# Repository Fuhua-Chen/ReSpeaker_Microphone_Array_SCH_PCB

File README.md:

# ReSpeaker_ReSpeaker_Microphone_Array_SCH_PCB
SCH, PCB and assembly files of ReSpeaker Microphone Array

## Requirements  
* Eagle v6.4 or later version

## Structure
* Folder SCH&PCB: sch, PCB and pdf built by Eagle
* Folder Assembly: Gerber, SMT coordinate, Assembly drawings

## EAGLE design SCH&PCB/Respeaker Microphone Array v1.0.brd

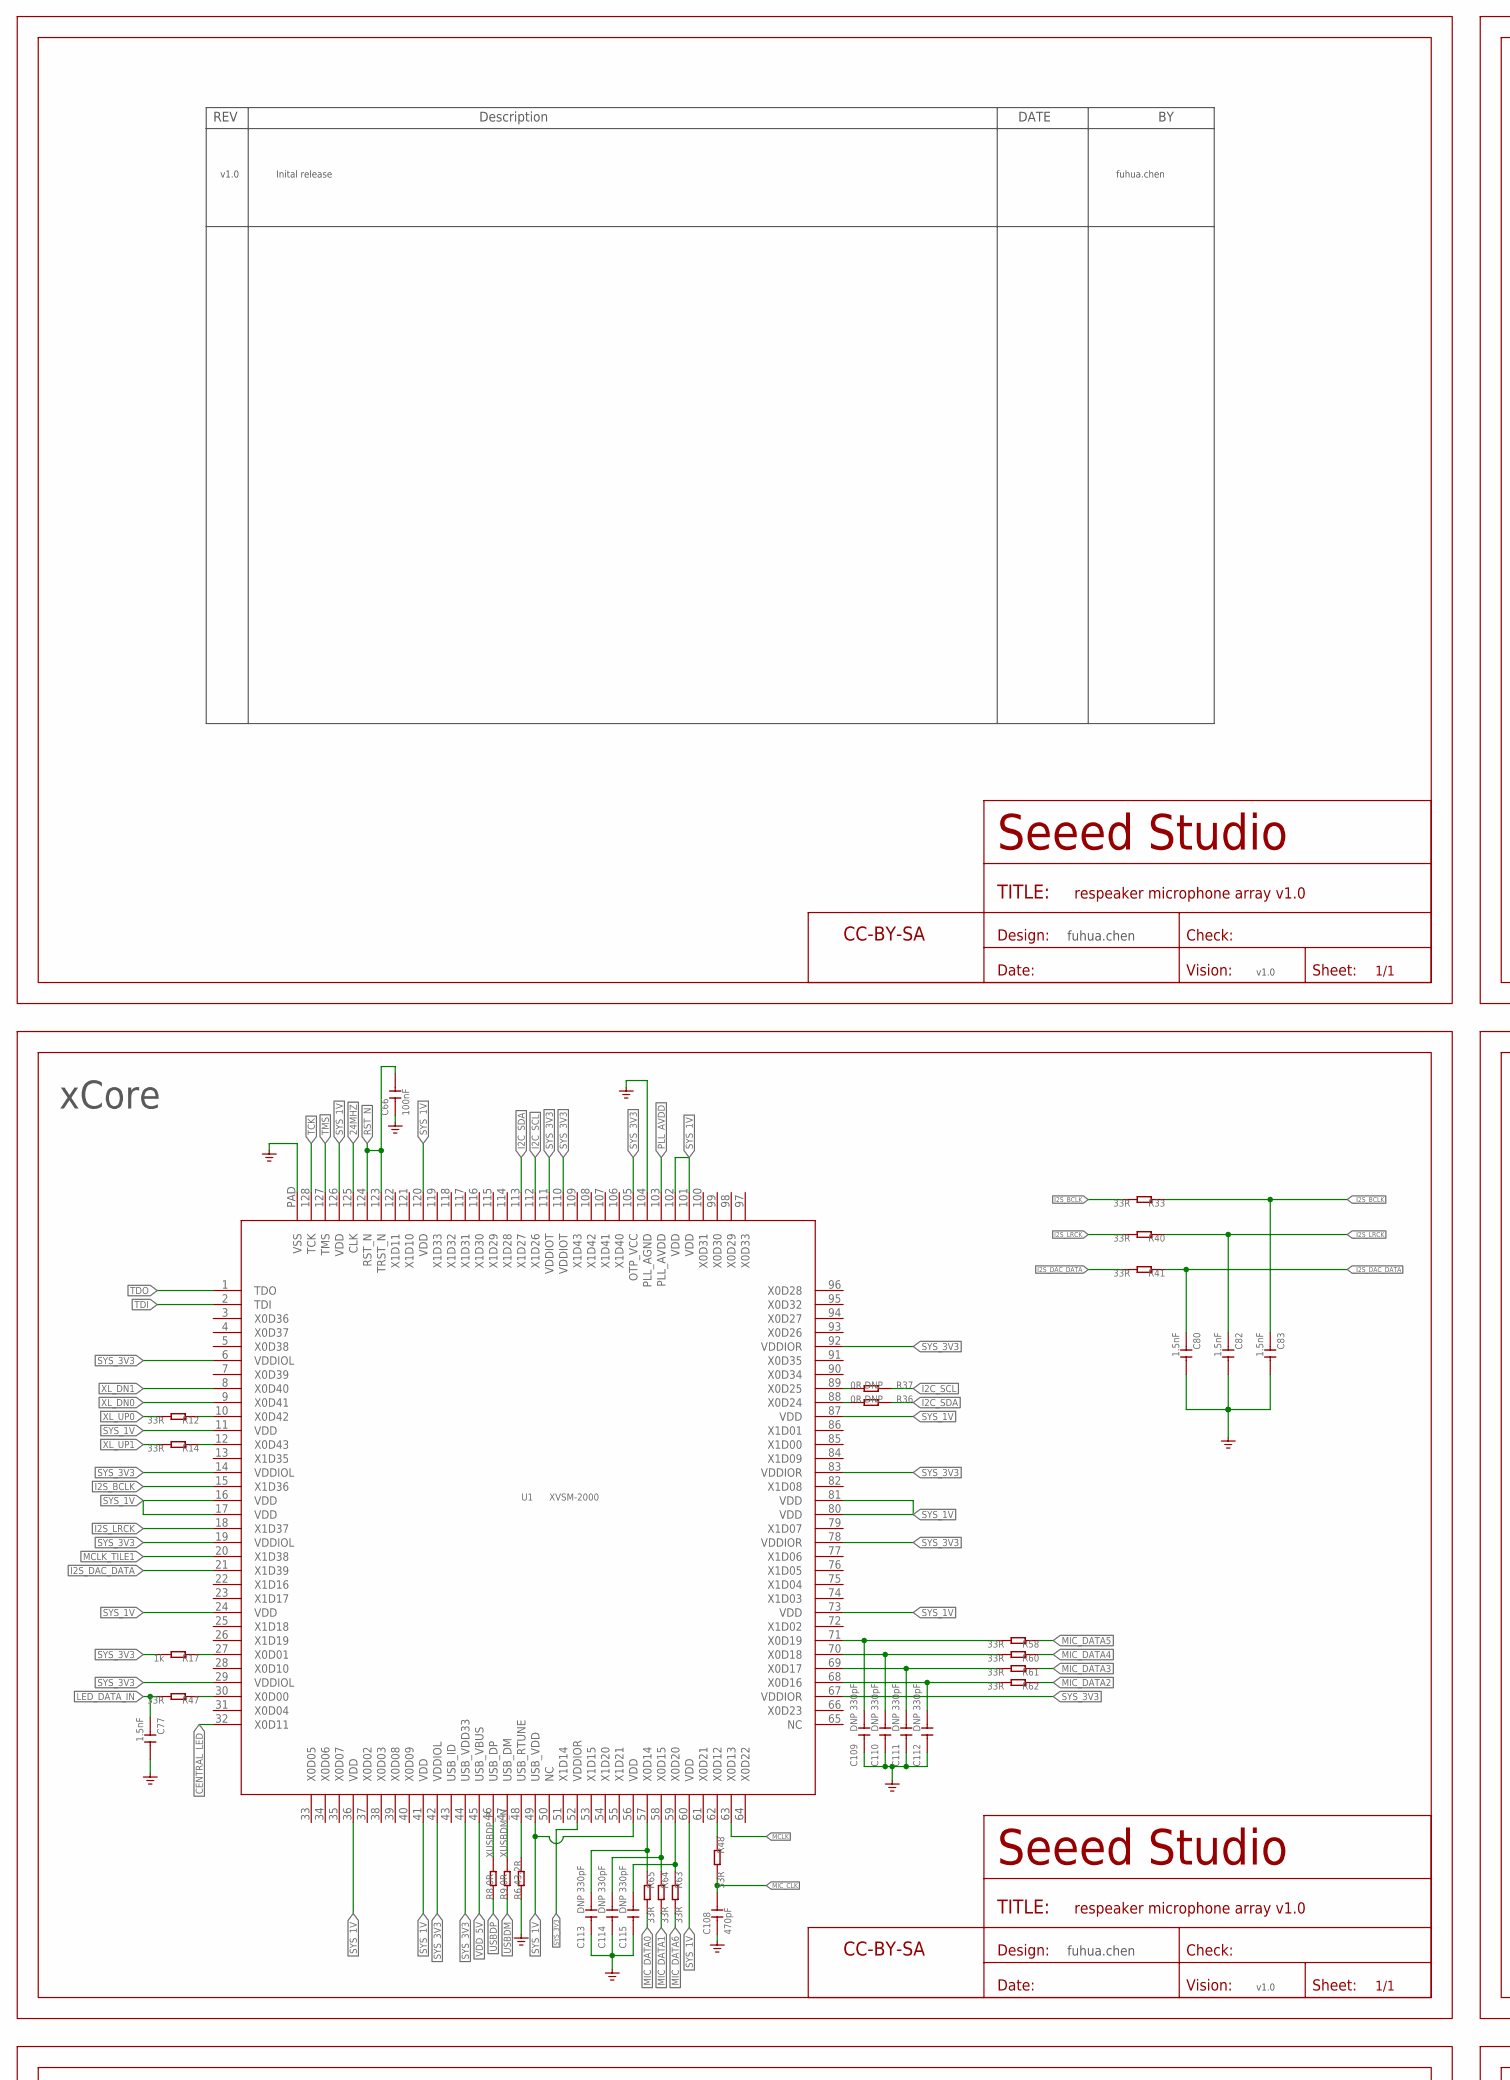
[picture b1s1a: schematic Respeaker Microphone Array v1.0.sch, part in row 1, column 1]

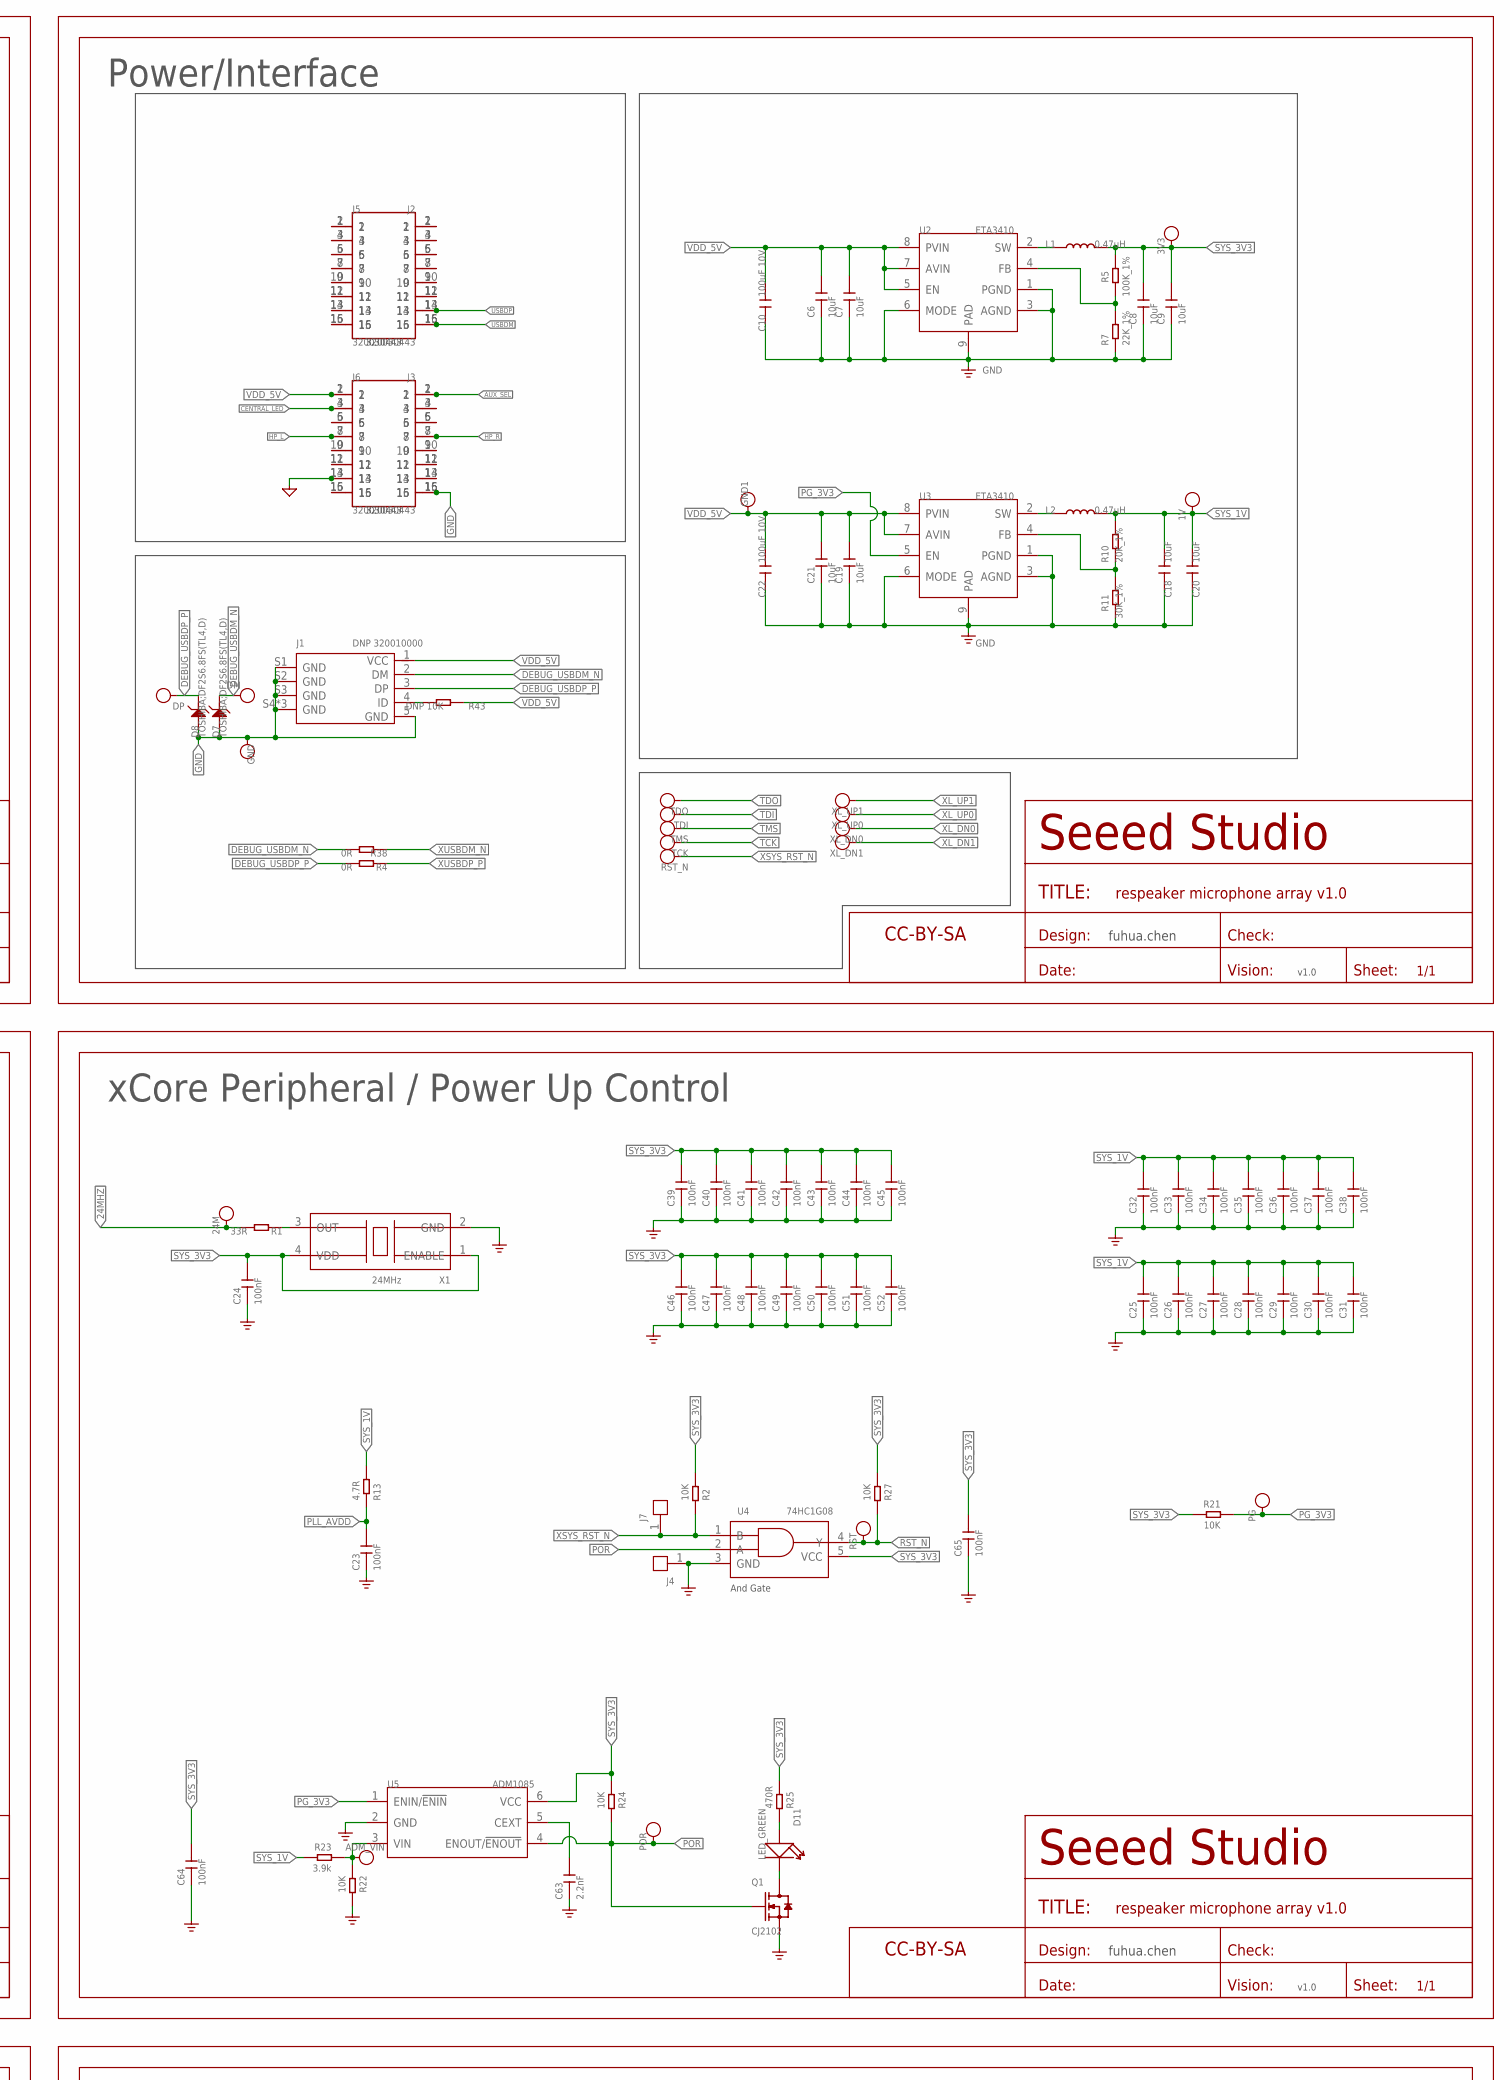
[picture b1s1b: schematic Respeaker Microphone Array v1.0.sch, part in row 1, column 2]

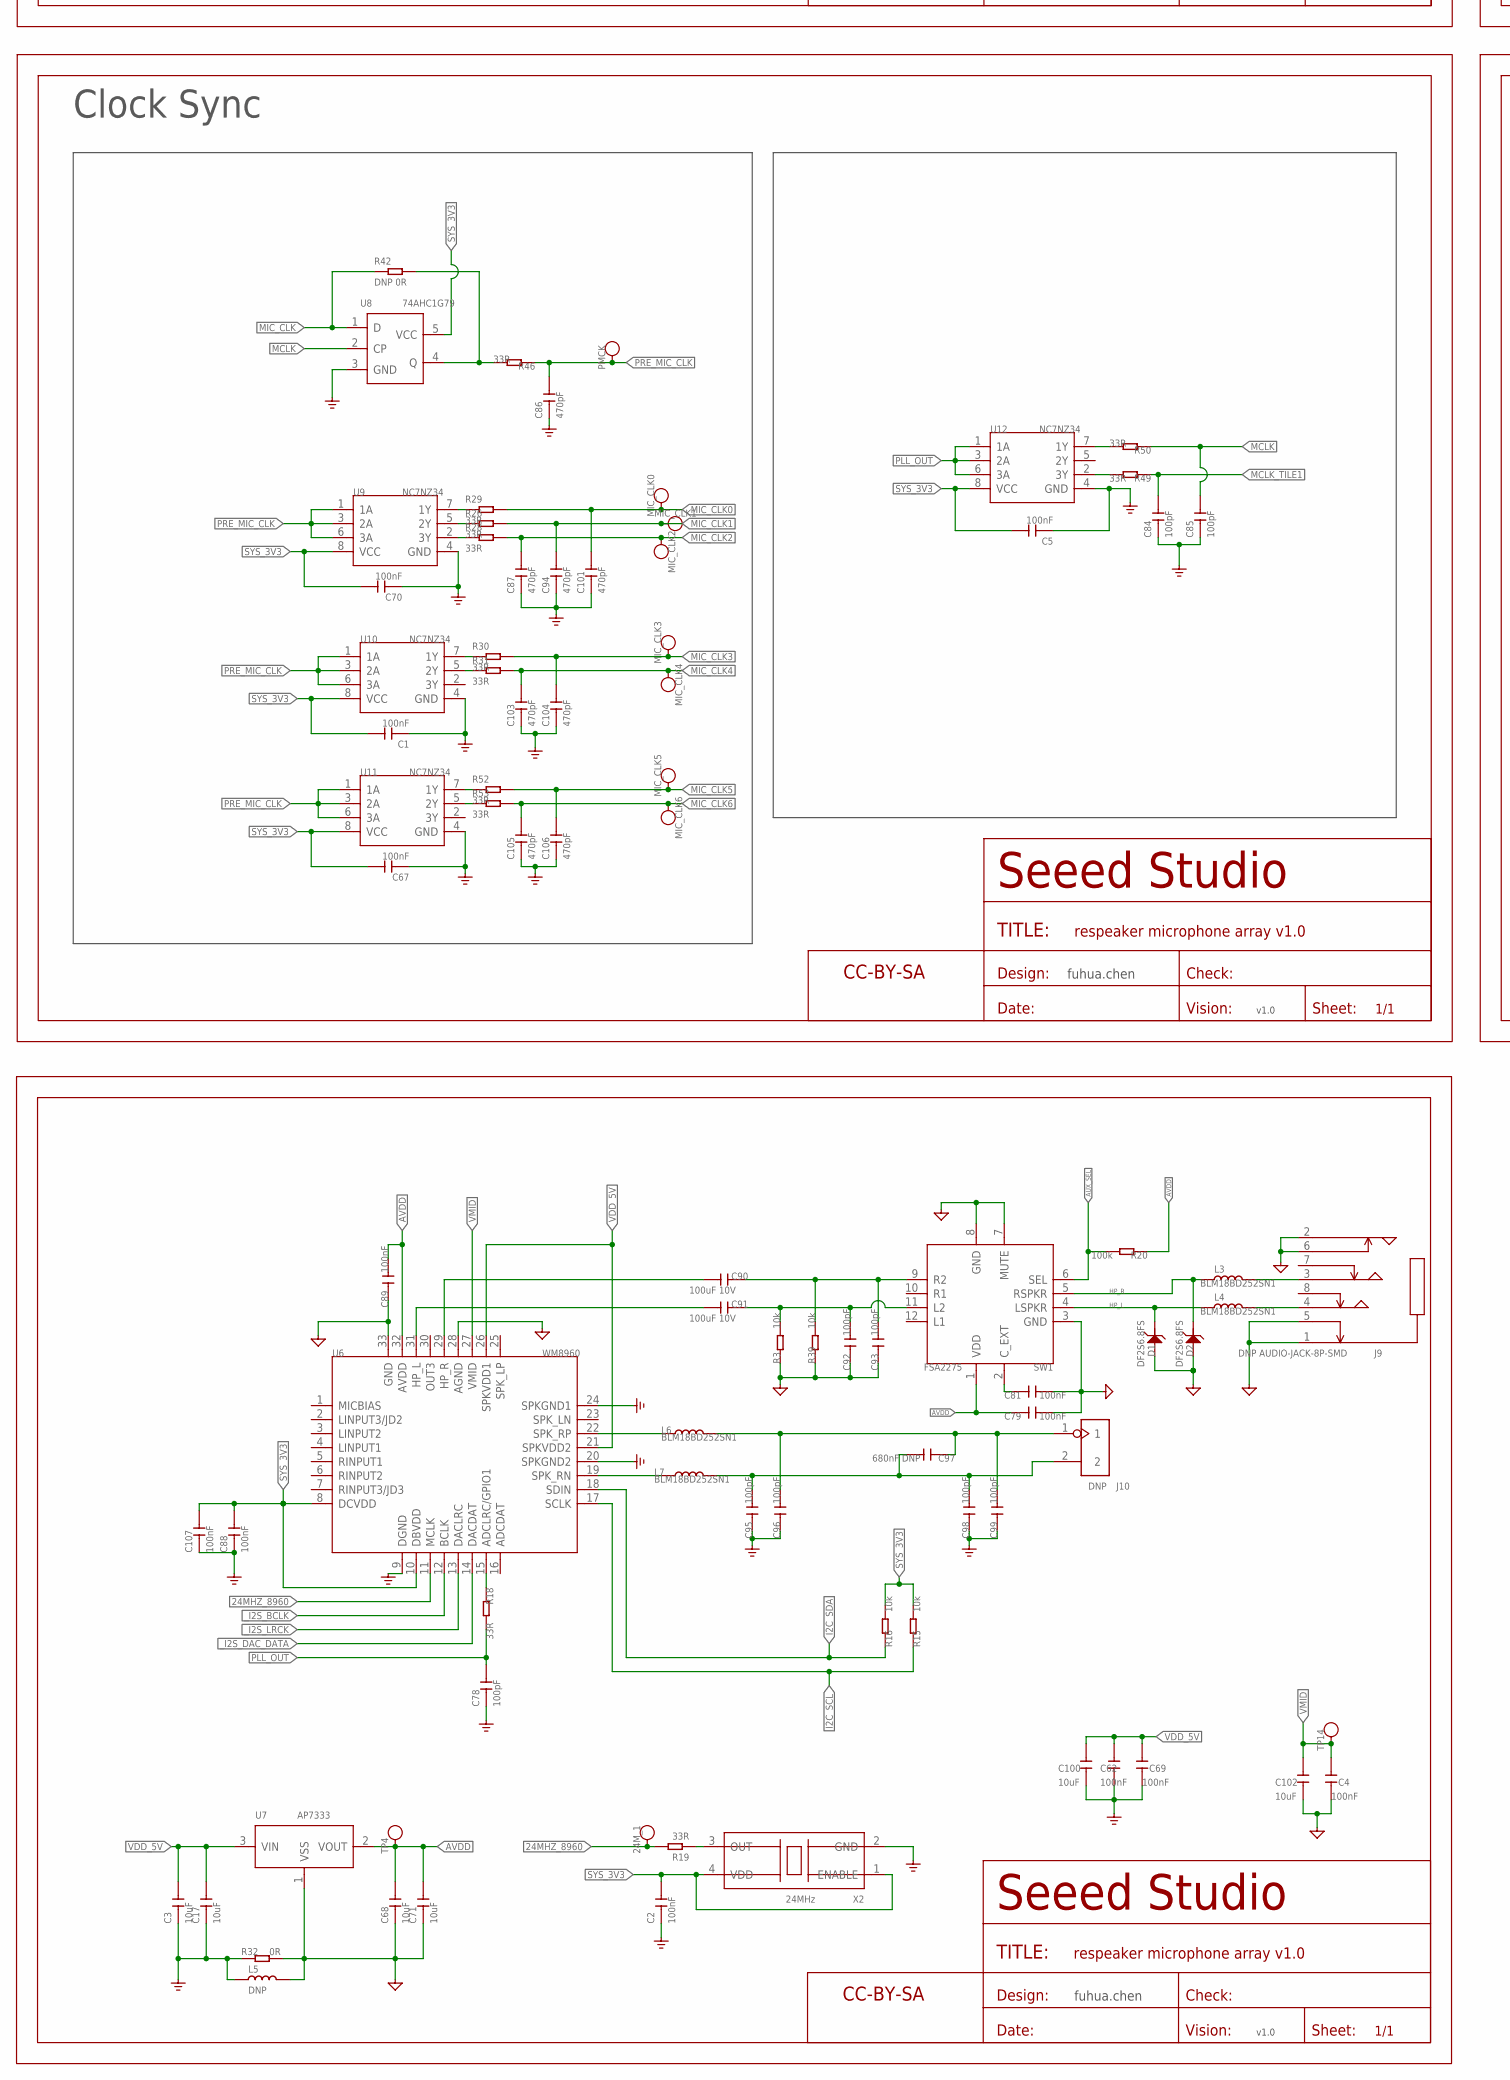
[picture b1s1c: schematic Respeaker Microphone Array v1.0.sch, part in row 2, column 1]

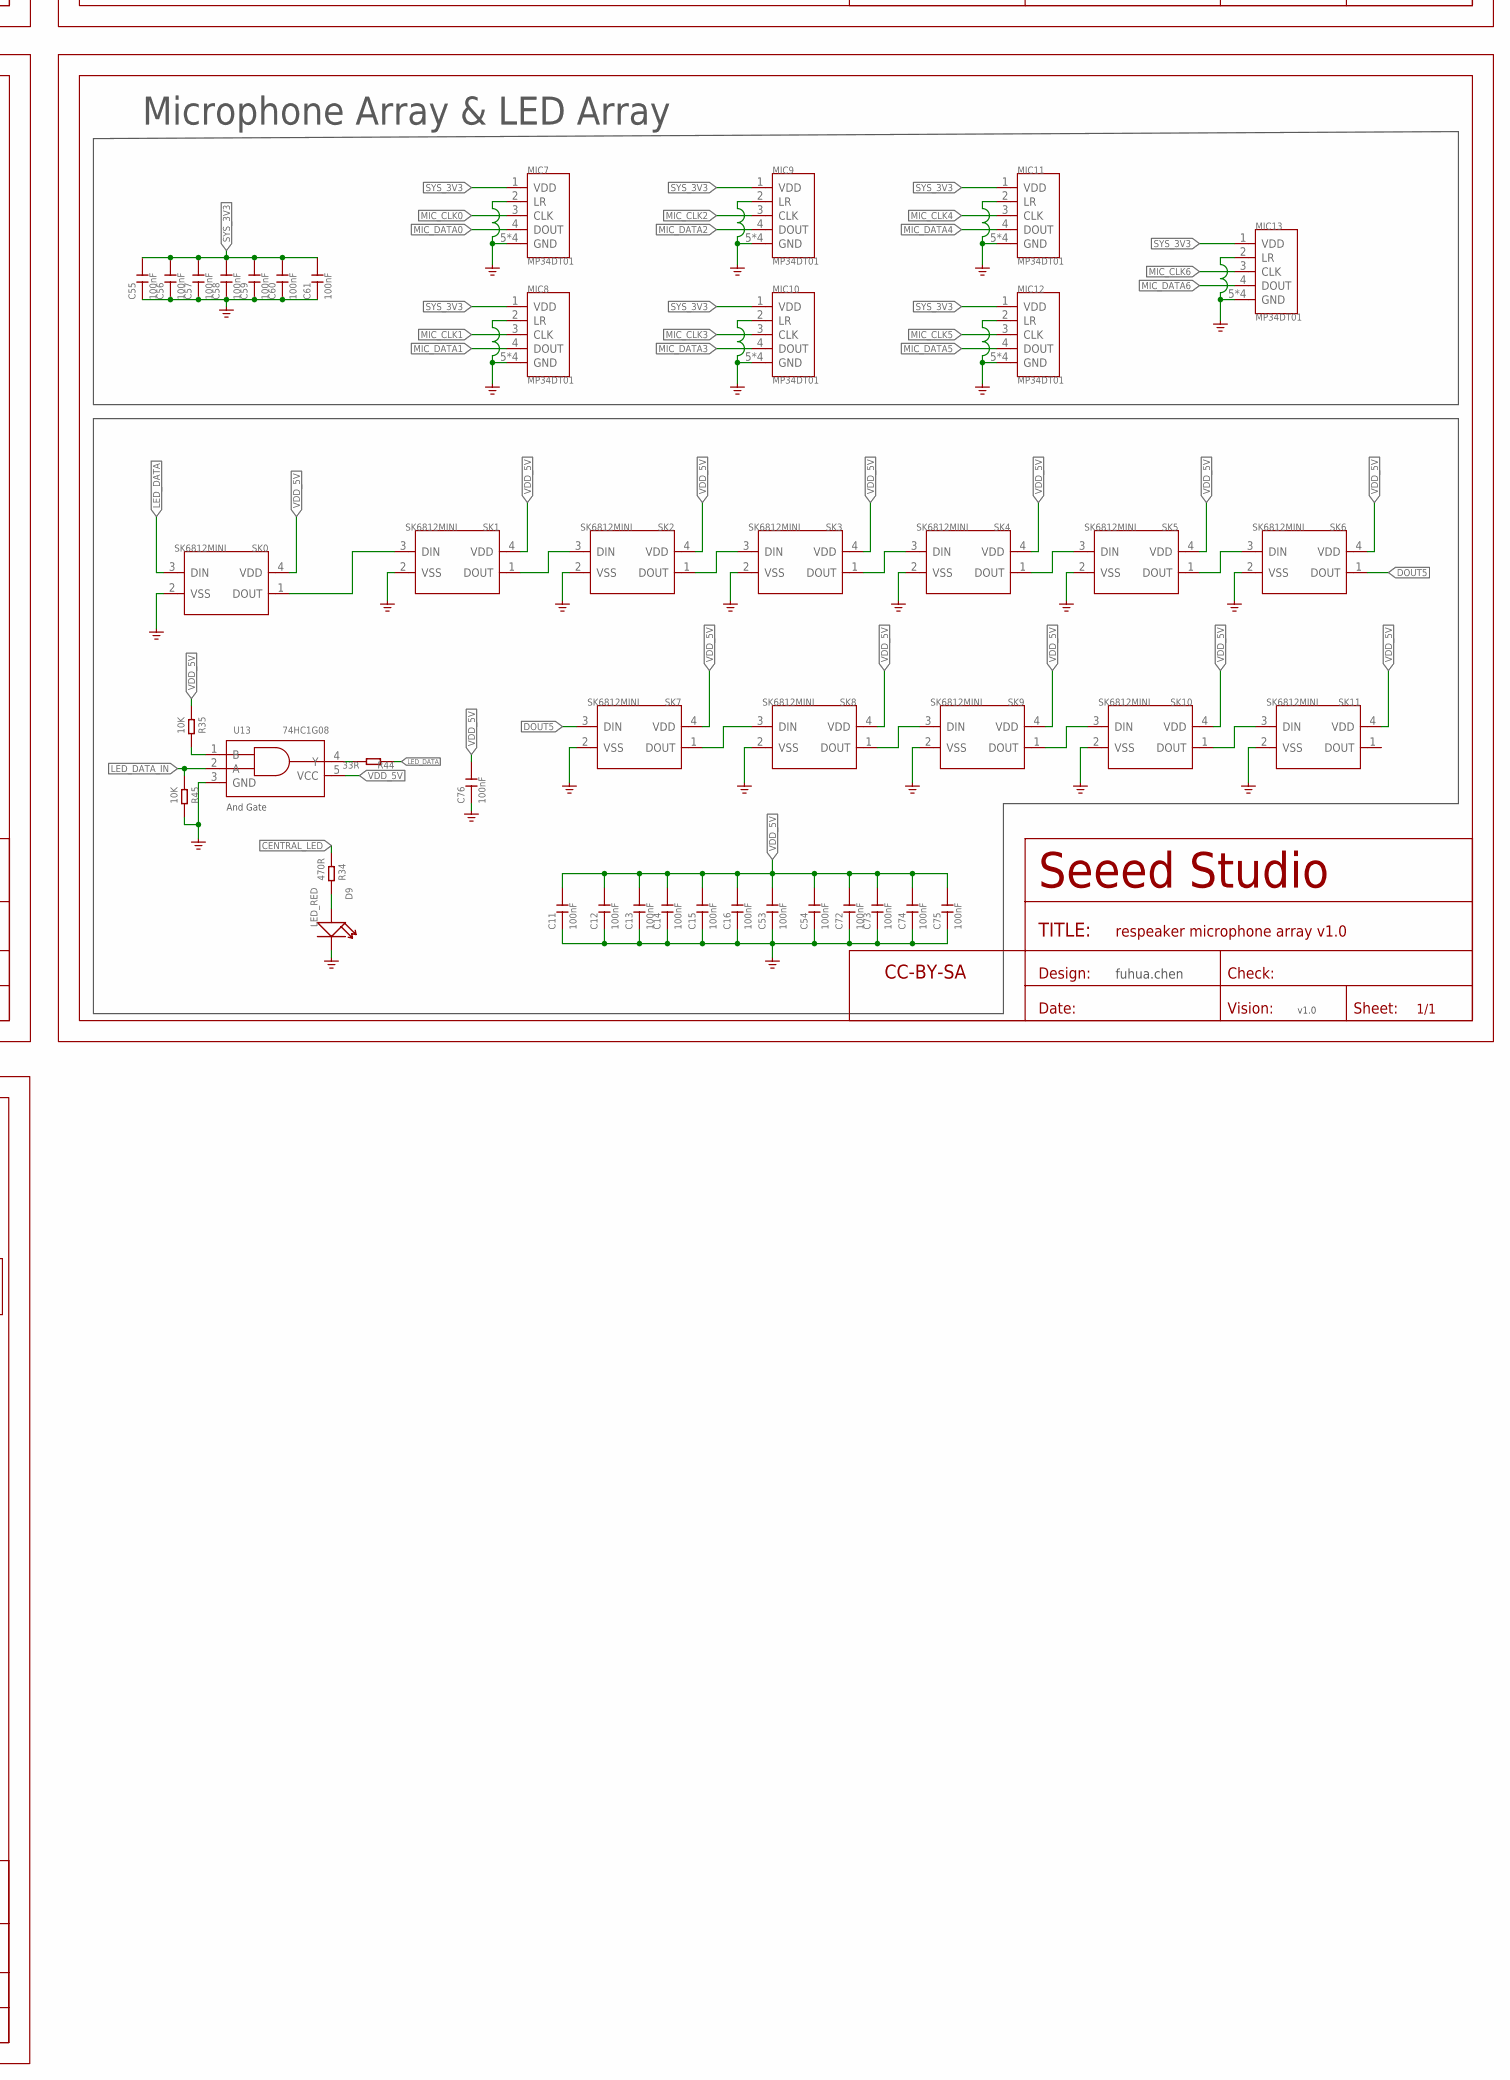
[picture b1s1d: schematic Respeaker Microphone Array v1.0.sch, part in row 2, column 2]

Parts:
1V, 3V3, 24M, 24M_1: TEST-POINT'4545'; TP-D45MIL
ADM_VIN: TEST-POINT'4545'; TP-D45MIL
C1, C2, C4, C5, C11, C12, C13, C14, C15, C16, C23, C24, C25, C26, C27, C28, C29, C30, C31, C32, C33, C34, C35, C36, C37, C38, C39, C40, C41, C42, C43, C44, C45, C46, C47, C48, C49, C50, C51, C52, C53, C54, C55, C56, C57, C58, C59, C60, C61, C62, C64, C65, C66, C67, C69, C70, C72, C73, C74, C75, C76, C79, C81, C88, C89, C107: 100nF; C0402
C3, C6, C7, C8, C9, C17, C18, C19, C20, C21, C68, C71, C100, C102: 10uF; C0603
C10, C22, C90, C91: 100uF 10V; C1206
C63: 2.2nF; C0402
C77, C80, C82, C83: 1.5nF; C0402
C78, C84, C85, C92, C93, C95, C96, C98, C99: 100pF; C0402
C86, C87, C94, C101, C103, C104, C105, C106, C108: 470pF; C0402
C97: 680nF DNP; C0402
C109, C110, C111, C112, C113, C114, C115: DNP 330pF; C0402
D1, D2: DF2S6.8FS; SOD-923
D7, D8: TOSHIBA;DF2S6.8FS(TL4,D); SOD-923
D9: LED_RED; LED-0402
D11: LED_GREEN; LED-0402
DM: TEST-POINT'4545'; TP-D45MIL
DP: TEST-POINT'4545'; TP-D45MIL
FR1, FR2, FR3, FR4, FR5, FR7, FR8: SEEEDSTUDIO-OPEN-SCH-FRAME; SEEEDSTUDIO-PCB-FRAME
GND, GND1: TEST-POINT'4545'; TP-D45MIL
J1: DNP 320010000; MICRO-USB5+4P-SMD-0.65-B
J2, J3, J5, J6: 320030443; H2X8-SMD-2.0
J4, J7: HEADER-1P'20'; 1P-40/25MIL
J9: DNP AUDIO-JACK-8P-SMD; AUDIO8P-SMD-3.5-14.5X6.1X4.0MM
J10: DNP; H2-2.54
L1, L2: 0.47uH; L201610
L3, L4, L6, L7: BLM18BD252SN1; L0603
L5: DNP; L0603
MIC7, MIC8, MIC9, MIC10, MIC11, MIC12, MIC13: MP34DT01; HCLGA5P-3X4X1MM
MIC_CLK0, MIC_CLK1, MIC_CLK2, MIC_CLK3, MIC_CLK4, MIC_CLK5, MIC_CLK6: TEST-POINT'4545'; TP-D45MIL
PG: TEST-POINT'4545'; TP-D45MIL
PMCK: TEST-POINT'4545'; TP-D45MIL
POR: TEST-POINT'4545'; TP-D45MIL
Q1: CJ2102; SOT-323
R1, R12, R14, R18, R19, R26, R28, R29, R30, R31, R33, R40, R41, R44, R46, R47, R48, R49, R50, R52, R53, R58, R60, R61, R62, R63, R64, R65: 33R; R0402
R2, R21, R22, R24, R27, R35, R45: 10K; R0402
R3, R15, R16, R39: 10k; R0402
R4, R8, R9, R32, R38: 0R; R0402
R5: 100K_1%; R0402
R6: 43.2R; R0402
R7: 22K_1%; R0402
R10: 20K_1%; R0402
R11: 30K_1%; R0402
R13: 4.7R; R0805
R17: 1k; R0402
R20: 100k; R0402
R23: 3.9k; R0402
R25, R34: 470R; R0402
R36, R37: 0R DNP; R0402
R42: DNP 0R; R0402
R43: DNP 10K; R0402
RST: TEST-POINT'4545'; TP-D45MIL
RST_N: TEST-POINT'4545'; TP-D45MIL
SK0, SK1, SK2, SK3, SK4, SK5, SK6, SK7, SK8, SK9, SK10, SK11: SK6812MINI; LED4-SMD-3.5X3.7MM
SW1: FSA2275; LEAD12P-SMD-0.4-1.8X1.8X0.5MM
TCK: TEST-POINT'4545'; TP-D45MIL
TDI: TEST-POINT'4545'; TP-D45MIL
TDO: TEST-POINT'4545'; TP-D45MIL
TMS: TEST-POINT'4545'; TP-D45MIL
TP4, TP14: TEST-POINT'4545'; TP-D45MIL
U1: XVSM-2000; TQFP128-0.4-14X14MM
U2, U3: ETA3410; DFN8G-0.5-2X2MM
U4, U13: 74HC1G08; SOT-353
U5: ADM1085; SC-70-6
U6: WM8960; QFN32G-0.5-5X5MM
U7: AP7333; SOT-23
U8: 74AHC1G79; SOT-353
U9, U10, U11, U12: NC7NZ34; US-8
X1, X2: 24MHz; OSC-SMD-2.5X2.0X0.9MM
XL_DN0, XL_DN1: TEST-POINT'4545'; TP-D45MIL
XL_UP0, XL_UP1: TEST-POINT'4545'; TP-D45MIL

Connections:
24MHZ: 24M.T, R1.2, U1.125 (CLK)
24MHZ_8960: 24M_1.T, R19.2, U6.11 (MCLK)
$123: C90.1, U6.29 (HP_R)
$124: C91.1, U6.31 (HP_L)
AGND: C4.1, C68.1, C71.1, C79.1, C81.1, C89.1, C92.1, C93.1, C102.2, D1.2 (1), D2.2 (1), J3.14, J6.13, J9.1, J9.2, J9.5, J9.6, L5.2, R3.1, R32.2, R39.1, SW1.3 (GND), SW1.7 (MUTE), SW1.8 (GND), U6.28 (AGND), U6.33 (GND), U7.1 (VSS)
AUX_SEL: J3.1, J6.2, R20.2, SW1.6 (SEL)
AVDD: C68.2, C71.2, C79.2, C89.2, R20.1, SW1.1 (VDD), TP4.T, U6.32 (AVDD), U7.2 (VOUT)
CENTRAL_LED: J3.4, J6.3, R34.2, U1.32 (X0D11)
DEBUG_USBDM_N: D7.1 (2), DM.T, J1.2 (DM), R38.2
DEBUG_USBDP_P: D8.1 (2), DP.T, J1.3 (DP), R4.2
DOUT5: SK6.1 (DOUT), SK7.3 (DIN)
GND: C1.1, C2.1, C3.1, C5.1, C6.1, C7.1, C8.1, C9.1, C10.1, C11.1, C12.1, C13.1, C14.1, C15.1, C16.1, C17.1, C18.1, C19.1, C20.1, C21.1, C22.1, C23.1, C24.1, C25.1, C26.1, C27.1, C28.1, C29.1, C30.1, C31.1, C32.1, C33.1, C34.1, C35.1, C36.1, C37.1, C38.1, C39.1, C40.1, C41.1, C42.1, C43.1, C44.1, C45.1, C46.1, C47.1, C48.1, C49.1, C50.1, C51.1, C52.1, C53.1, C54.1, C55.1, C56.1, C57.1, C58.1, C59.1, C60.1, C61.1, C62.1, C63.1, C64.1, C65.1, C66.1, C67.1, C69.1, C70.1, C72.1, C73.1, C74.1, C75.1, C76.1, C77.2, C78.1, C80.2, C82.2, C83.2, C84.1, C85.1, C86.1, C87.1, C88.1, C94.1, C95.1, C96.1, C98.1, C99.1, C100.2, C101.1, C103.1, C104.1, C105.1, C106.1, C107.1, C108.1, C109.1, C110.1, C111.1, C112.1, C113.1, C114.1, C115.1, D7.2 (1), D8.2 (1), D9.-, GND.T, J1.5 (GND), J1.S1 (GND), J1.S2 (GND), J1.S3 (GND), J1.S4 (GND), J1.S5 (GND), J1.S6 (GND), J3.15, J4.1, J6.16, L5.1, MIC7.2 (LR), MIC7.5 (GND), MIC7.6 (GND), MIC7.7 (GND), MIC7.8 (GND), MIC8.2 (LR), MIC8.5 (GND), MIC8.6 (GND), MIC8.7 (GND), MIC8.8 (GND), MIC9.2 (LR), MIC9.5 (GND), MIC9.6 (GND), MIC9.7 (GND), MIC9.8 (GND), MIC10.2 (LR), MIC10.5 (GND), MIC10.6 (GND), MIC10.7 (GND), MIC10.8 (GND), MIC11.2 (LR), MIC11.5 (GND), MIC11.6 (GND), MIC11.7 (GND), MIC11.8 (GND), MIC12.2 (LR), MIC12.5 (GND), MIC12.6 (GND), MIC12.7 (GND), MIC12.8 (GND), MIC13.2 (LR), MIC13.5 (GND), MIC13.6 (GND), MIC13.7 (GND), MIC13.8 (GND), Q1.2 (S), R6.1, R7.1, R11.1, R22.1, R32.1, R45.1, SK0.2 (VSS), SK1.2 (VSS), SK2.2 (VSS), SK3.2 (VSS), SK4.2 (VSS), SK5.2 (VSS), SK6.2 (VSS), SK7.2 (VSS), SK8.2 (VSS), SK9.2 (VSS), SK10.2 (VSS), SK11.2 (VSS), U1.104 (PLL_AGND), U1.PAD (VSS), U2.1 (PGND), U2.3 (AGND), U2.6 (MODE), U2.9 (PAD), U3.1 (PGND), U3.3 (AGND), U3.6 (MODE), U3.9 (PAD), U4.3 (GND), U5.2 (GND), U6.9 (DGND), U6.20 (SPKGND2), U6.24 (SPKGND1), U8.3 (GND), U9.4 (GND), U10.4 (GND), U11.4 (GND), U12.4 (GND), U13.3 (GND), X1.2 (GND), X2.2 (GND)
HP_L: D1.1 (2), J3.8, J6.7, L4.1, SW1.4 (LSPKR)
HP_R: D2.1 (2), J3.7, J6.8, L3.1, SW1.5 (RSPKR)
I2C_SCL: R15.1, R37.1, U1.112 (X1D26), U6.17 (SCLK)
I2C_SDA: R16.1, R36.1, U1.113 (X1D27), U6.18 (SDIN)
I2S_BCLK: R33.2, U1.15 (X1D36)
I2S_DAC_DATA: R41.2, U1.21 (X1D39)
I2S_LRCK: R40.2, U1.18 (X1D37)
LED_DATA: R44.1, SK0.3 (DIN)
LED_DATA_IN: C77.1, R45.2, R47.2, U13.2 (A)
MCLK: C85.2, R50.1, U1.63 (X0D13), U8.2 (CP)
MCLK_TILE1: C84.2, R49.1, U1.20 (X1D38)
MIC_CLK: C108.2, R42.1, R48.2, U8.1 (D)
MIC_CLK0: C101.2, MIC7.3 (CLK), MIC_CLK0.T, R29.2
MIC_CLK1: C94.2, MIC8.3 (CLK), MIC_CLK1.T, R26.2
MIC_CLK2: C87.2, MIC9.3 (CLK), MIC_CLK2.T, R28.2
MIC_CLK3: C104.2, MIC10.3 (CLK), MIC_CLK3.T, R30.2
MIC_CLK4: C103.2, MIC11.3 (CLK), MIC_CLK4.T, R31.2
MIC_CLK5: C106.2, MIC12.3 (CLK), MIC_CLK5.T, R52.2
MIC_CLK6: C105.2, MIC13.3 (CLK), MIC_CLK6.T, R53.2
MIC_DATA0: MIC7.4 (DOUT), R65.2
MIC_DATA1: MIC8.4 (DOUT), R64.2
MIC_DATA2: MIC9.4 (DOUT), R62.1
MIC_DATA3: MIC10.4 (DOUT), R61.1
MIC_DATA4: MIC11.4 (DOUT), R60.1
MIC_DATA5: MIC12.4 (DOUT), R58.1
MIC_DATA6: MIC13.4 (DOUT), R63.2
unnamed: R14.1, U1.12 (X0D43)
unnamed: R18.1, U6.15 (ADCLRC/GPIO1)
unnamed: L2.1, U3.2 (SW)
unnamed: R6.2, U1.48 (USB_RTUNE)
unnamed: R12.1, U1.10 (X0D42)
unnamed: R17.1, U1.27 (X0D01)
unnamed: ADM_VIN.T, R22.2, R23.1, U5.3 (VIN)
unnamed: R10.1, R11.2, U3.4 (FB)
unnamed: D11.-, Q1.3 (D)
unnamed: SK8.1 (DOUT), SK9.3 (DIN)
unnamed: R1.1, X1.3 (OUT)
unnamed: D11.+, R25.1
unnamed: SK1.1 (DOUT), SK2.3 (DIN)
unnamed: C63.2, U5.5 (CEXT)
unnamed: R28.1, U9.2 (3Y)
unnamed: R53.1, U11.5 (2Y)
unnamed: SK2.1 (DOUT), SK3.3 (DIN)
unnamed: C81.2, SW1.2 (C_EXT)
unnamed: SK3.1 (DOUT), SK4.3 (DIN)
unnamed: SK4.1 (DOUT), SK5.3 (DIN)
unnamed: R19.1, X2.3 (OUT)
unnamed: R26.1, U9.5 (2Y)
unnamed: R31.1, U10.5 (2Y)
unnamed: R29.1, U9.7 (1Y)
unnamed: R49.2, U12.2 (3Y)
unnamed: R50.2, U12.7 (1Y)
unnamed: J2.1, J5.2
unnamed: R30.1, U10.7 (1Y)
unnamed: L1.1, U2.2 (SW)
unnamed: J2.2, J5.1
unnamed: R47.1, U1.30 (X0D00)
unnamed: R5.1, R7.2, U2.4 (FB)
unnamed: R52.1, U11.7 (1Y)
unnamed: J2.3, J5.4
unnamed: C109.2, R58.2, U1.71 (X0D19)
unnamed: C110.2, R60.2, U1.70 (X0D18)
unnamed: C111.2, R61.2, U1.69 (X0D17)
unnamed: C112.2, R62.2, U1.68 (X0D16)
unnamed: C115.2, R63.1, U1.59 (X0D20)
unnamed: C114.2, R64.1, U1.58 (X0D15)
unnamed: J3.5, J6.6
unnamed: J1.4 (ID), R43.2
unnamed: SK5.1 (DOUT), SK6.3 (DIN)
unnamed: SK7.1 (DOUT), SK8.3 (DIN)
unnamed: R36.2, U1.88 (X0D24)
unnamed: SK9.1 (DOUT), SK10.3 (DIN)
unnamed: SK10.1 (DOUT), SK11.3 (DIN)
unnamed: SK0.1 (DOUT), SK1.3 (DIN)
unnamed: D9.+, R34.1
unnamed: J2.4, J5.3
unnamed: J2.5, J5.6
unnamed: R37.2, U1.89 (X0D25)
unnamed: C95.2, C97.2, C98.2, J10.2, L7.2
unnamed: J9.3, L3.2
unnamed: C90.2, C93.2, R39.2, SW1.9 (R2)
unnamed: J9.4, L4.2
unnamed: J2.6, J5.5
unnamed: J2.7, J5.8
unnamed: J2.8, J5.7
unnamed: C91.2, C92.2, R3.2, SW1.11 (L2)
unnamed: L6.1, U6.22 (SPK_RP)
unnamed: J2.9, J5.10
unnamed: J2.10, J5.9
unnamed: L7.1, U6.19 (SPK_RN)
unnamed: C96.2, C97.1, C99.2, J10.1, L6.2
unnamed: J2.11, J5.12
unnamed: J2.12, J5.11
unnamed: J2.14, J5.13
unnamed: J2.16, J5.15
unnamed: R44.2, U13.4 (Y)
unnamed: R35.1, U13.1 (B)
unnamed: J3.6, J6.5
unnamed: J3.9, J6.10
unnamed: J3.10, J6.9
unnamed: J3.11, J6.12
unnamed: J3.12, J6.11
unnamed: J3.13, J6.14
unnamed: J3.16, J6.15
unnamed: R42.2, R46.2, U8.4 (Q)
unnamed: R48.1, U1.62 (X0D12)
unnamed: C113.2, R65.1, U1.57 (X0D14)
unnamed: J3.3, J6.4
PG_3V3: PG.T, R21.1, U3.5 (EN), U5.1 (ENIN/!ENIN)
PLL_AVDD: C23.2, R13.1, U1.103 (PLL_AVDD)
PLL_OUT: C78.2, R18.2, U12.1 (1A), U12.3 (2A), U12.6 (3A)
POR: POR.T, Q1.1 (G), R24.1, U4.2 (A), U5.4 (ENOUT/!ENOUT)
PRE_MIC_CLK: C86.2, PMCK.T, R46.1, U9.1 (1A), U9.3 (2A), U9.6 (3A), U10.1 (1A), U10.3 (2A), U10.6 (3A), U11.1 (1A), U11.3 (2A), U11.6 (3A)
RST_N: C66.2, R27.1, RST.T, U1.123 (TRST_N), U1.124 (RST_N), U4.4 (Y)
SYS_1V: 1V.T, C18.2, C20.2, C25.2, C26.2, C27.2, C28.2, C29.2, C30.2, C31.2, C32.2, C33.2, C34.2, C35.2, C36.2, C37.2, C38.2, L2.2, R10.2, R13.2, R23.2, U1.11 (VDD), U1.16 (VDD), U1.17 (VDD), U1.24 (VDD), U1.36 (VDD), U1.41 (VDD), U1.49 (USB_VDD), U1.56 (VDD), U1.60 (VDD), U1.73 (VDD), U1.80 (VDD), U1.81 (VDD), U1.87 (VDD), U1.101 (VDD), U1.102 (VDD), U1.120 (VDD), U1.126 (VDD)
SYS_3V3: 3V3.T, C1.2, C2.2, C5.2, C8.2, C9.2, C24.2, C39.2, C40.2, C41.2, C42.2, C43.2, C44.2, C45.2, C46.2, C47.2, C48.2, C49.2, C50.2, C51.2, C52.2, C55.2, C56.2, C57.2, C58.2, C59.2, C60.2, C61.2, C64.2, C65.2, C67.2, C70.2, C88.2, C107.2, L1.2, MIC7.1 (VDD), MIC8.1 (VDD), MIC9.1 (VDD), MIC10.1 (VDD), MIC11.1 (VDD), MIC12.1 (VDD), MIC13.1 (VDD), R2.2, R5.2, R15.2, R16.2, R17.2, R21.2, R24.2, R25.2, R27.2, U1.6 (VDDIOL), U1.14 (VDDIOL), U1.19 (VDDIOL), U1.29 (VDDIOL), U1.42 (VDDIOL), U1.44 (USB_VDD33), U1.52 (VDDIOR), U1.67 (VDDIOR), U1.78 (VDDIOR), U1.83 (VDDIOR), U1.92 (VDDIOR), U1.105 (OTP_VCC), U1.110 (VDDIOT), U1.111 (VDDIOT), U4.5 (VCC), U5.6 (VCC), U6.8 (DCVDD), U6.10 (DBVDD), U8.5 (VCC), U9.8 (VCC), U10.8 (VCC), U11.8 (VCC), U12.8 (VCC), X1.1 (ENABLE), X1.4 (VDD), X2.1 (ENABLE), X2.4 (VDD)
TCK: TCK.T, U1.128 (TCK)
TDI: TDI.T, U1.2 (TDI)
TDO: TDO.T, U1.1 (TDO)
TMS: TMS.T, U1.127 (TMS)
USBDM: J2.15, J5.16, R9.1
USBDP: J2.13, J5.14, R8.1
VDD_5V: C3.2, C6.2, C7.2, C10.2, C11.2, C12.2, C13.2, C14.2, C15.2, C16.2, C17.2, C19.2, C21.2, C22.2, C53.2, C54.2, C62.2, C69.2, C72.2, C73.2, C74.2, C75.2, C76.2, C100.1, GND1.T, J1.1 (VCC), J3.2, J6.1, R35.2, R43.1, SK0.4 (VDD), SK1.4 (VDD), SK2.4 (VDD), SK3.4 (VDD), SK4.4 (VDD), SK5.4 (VDD), SK6.4 (VDD), SK7.4 (VDD), SK8.4 (VDD), SK9.4 (VDD), SK10.4 (VDD), SK11.4 (VDD), U1.45 (USB_VBUS), U2.5 (EN), U2.7 (AVIN), U2.8 (PVIN), U3.7 (AVIN), U3.8 (PVIN), U6.21 (SPKVDD2), U6.26 (SPKVDD1), U7.3 (VIN), U13.5 (VCC)
VMID: C4.2, C102.1, TP14.T, U6.27 (VMID)
XL_DN0: U1.9 (X0D41), XL_DN0.T
XL_DN1: U1.8 (X0D40), XL_DN1.T
XL_UP0: R12.2, XL_UP0.T
XL_UP1: R14.2, XL_UP1.T
XSYS_RST_N: J7.1, R2.1, RST_N.T, U4.1 (B)
XUSBDM_N: R9.2, R38.1, U1.47 (USB_DM)
XUSBDP_P: R4.1, R8.2, U1.46 (USB_DP)
_I2S_BCLK: C83.1, R33.1, U6.12 (BCLK)
_I2S_DAC_DATA: C80.1, R41.1, U6.14 (DACDAT)
_I2S_LRCK: C82.1, R40.1, U6.13 (DACLRC)

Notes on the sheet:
fuhua.chen
xCore
Power/Interface
v1.0
Inital release
Microphone Array & LED Array
Clock Sync
And Gate
xCore Peripheral / Power Up Control

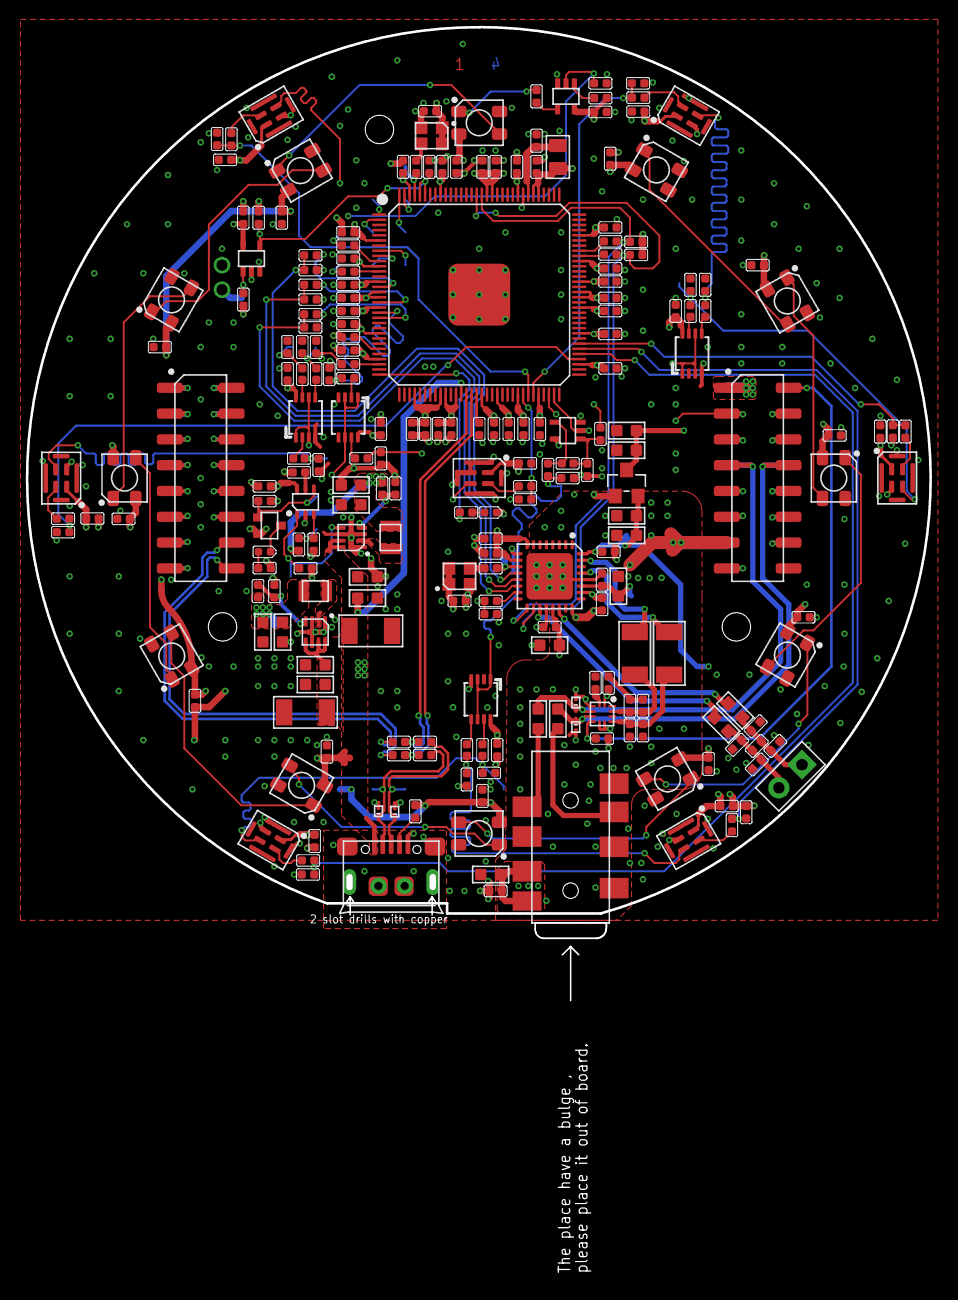
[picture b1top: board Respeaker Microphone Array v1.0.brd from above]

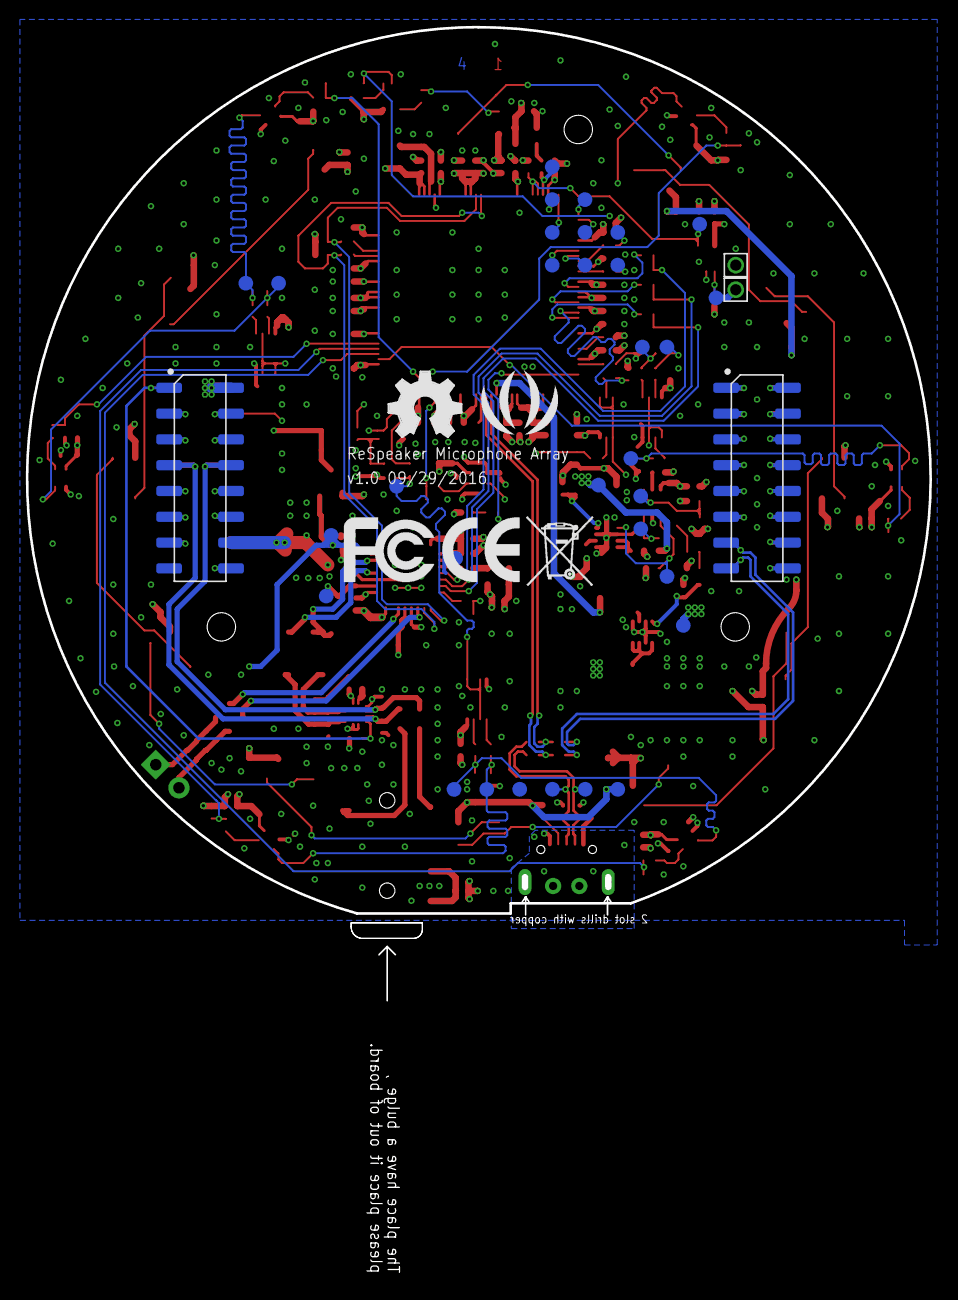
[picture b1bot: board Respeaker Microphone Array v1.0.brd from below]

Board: 4 copper layers, 70.1 x 75.5 mm, 272 parts (37 on the bottom side), 146 nets.

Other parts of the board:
U$36: OSHW_FILLX200_NOTEXT_TNAME
U$51: SEEED-SILK-TNAME-280*268MIL

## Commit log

2017-02-06 NPI commit
    NPI files
2017-02-06 README.md update
    update README

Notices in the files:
parts and their libraries:
moudle-new: This work is licensed under the Creative Commons Attribution 4.0 International License.
To view a copy of this license,visit:
http://creativecommons.org/licenses/by-sa/4.0
moudle-new: CC-BY-SA
